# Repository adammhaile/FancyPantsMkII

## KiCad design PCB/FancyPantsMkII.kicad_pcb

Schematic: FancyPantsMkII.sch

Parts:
C1, C2: 0.1uF; SparkFun-AXIAL-5MM
E1: ENCODER_SWITCH
IC1: ATMEGA1284P-P; DIL40
J1: J_SIGNAL
J2: J_DISPLAY
JP1: ICSP
JP2: FTDI; SparkFun-FTDI_BASIC
R1: 10K; SparkFun-AXIAL-0.4
S1: TAC_SWITCHPTH; SparkFun-TACTILE-PTH
Y1: 16MHz

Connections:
5VCC: C2.1, IC1.10 (VCC), IC1.30 (AVCC), J1.1, J2.7, JP1.2, JP2.VCC (4), R1.1
BTN: IC1.17 ((PCINT27/TXD1/INT1)PD3), S1.3, S1.4
DISP_RST: IC1.21 ((PCINT31/OC2A)PD7), J2.4
ENC_A: E1.1, IC1.16 ((PCINT26/RXD1/INT0)PD2)
ENC_B: E1.3, IC1.15 ((PCINT25/TXD0)PD1), JP2.RXI (2)
ENC_BTN: E1.5, IC1.3 ((PCINT10/AIN0/INT2)PB2)
GND: C2.2, E1.2, E1.4, IC1.11 (GND), IC1.31 (GND), J1.4, J2.8, JP1.6, JP2.CTS (5), JP2.GND (6), S1.1, S1.2, Y1.2
MISO: IC1.7 ((PCINT14/MISO)PB6), JP1.1
MOSI: IC1.6 ((PCINT13/MOSI)PB5), JP1.4
unnamed: C1.1, JP2.DTR (1)
NEOA: IC1.1 ((PCINT8/T0/XCK)PB0), J1.2
NEOB: IC1.2 ((PCINT9/CLKO/T1)PB1), J1.3
RST: C1.2, IC1.9 (~RESET), JP1.5, R1.2
SCK: IC1.8 ((PCINT15/SCK)PB7), JP1.3
SCL: IC1.22 ((PCINT16/SCL)PC0), J2.2
SDA: IC1.23 ((PCINT17/SDA)PC1), J2.1
TOSC1: IC1.13 (XTAL1), Y1.3
TOSC2: IC1.12 (XTAL2), Y1.1
TXO: IC1.14 ((PCINT24/RXD0)PD0), JP2.TXO (3)

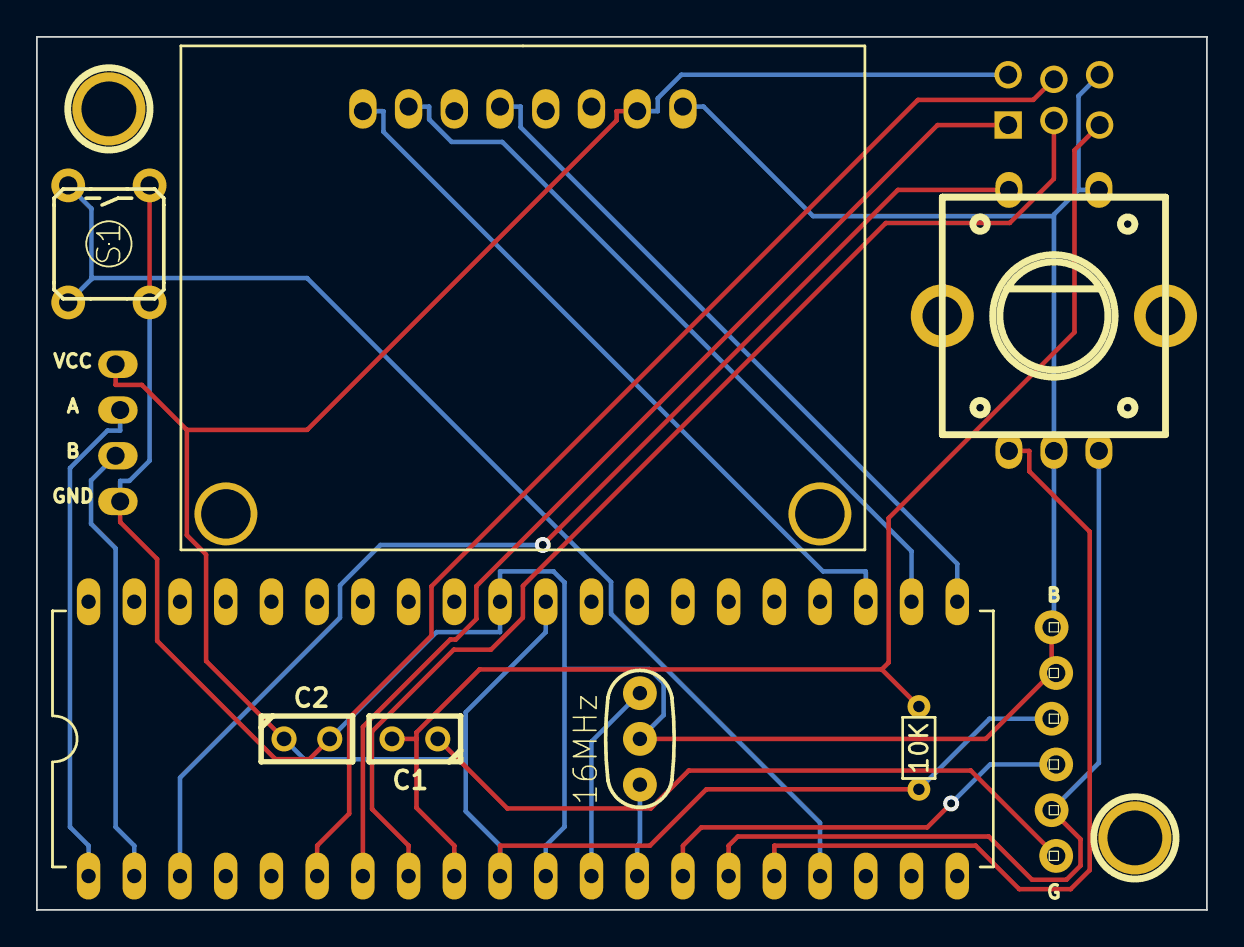
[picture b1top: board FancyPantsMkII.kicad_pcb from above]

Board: 2 copper layers, 65.0 x 48.5 mm, 13 parts (0 on the bottom side), 19 nets.

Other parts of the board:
1PIN1: p1; 1pin
1PIN2: p2; 1pin

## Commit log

2013-12-15 working override button
2013-12-20 added LEDs
2013-12-21 More menu depth
2013-12-21 Working brightness controls
2013-12-21 added max overload mode
2013-12-21 better var inits and more responsive brightness controll
2014-01-18 moved stuff around, added PCB
2014-01-20 added case 3D models
2014-01-22 added arm band 3D model
2014-01-23 tweaks
2014-02-06 updated animations and missing pixel fixes
2014-02-07 added custom 5x6 LED strip font and text output
2014-02-09 many many fixes and updates
2014-02-10 added demo mode
2014-02-10 more animations, faster override
2014-02-12 more animations
2014-02-16 added Game of Life animation
2014-02-18 added splash screen and a few other tweaks
2014-02-18 fixed display reset net name
    display reset net was named same as uC reset net, tying the two
    together. Will probably never remake this board, but needed to fix the
    net in case anyone else ever wants to.
